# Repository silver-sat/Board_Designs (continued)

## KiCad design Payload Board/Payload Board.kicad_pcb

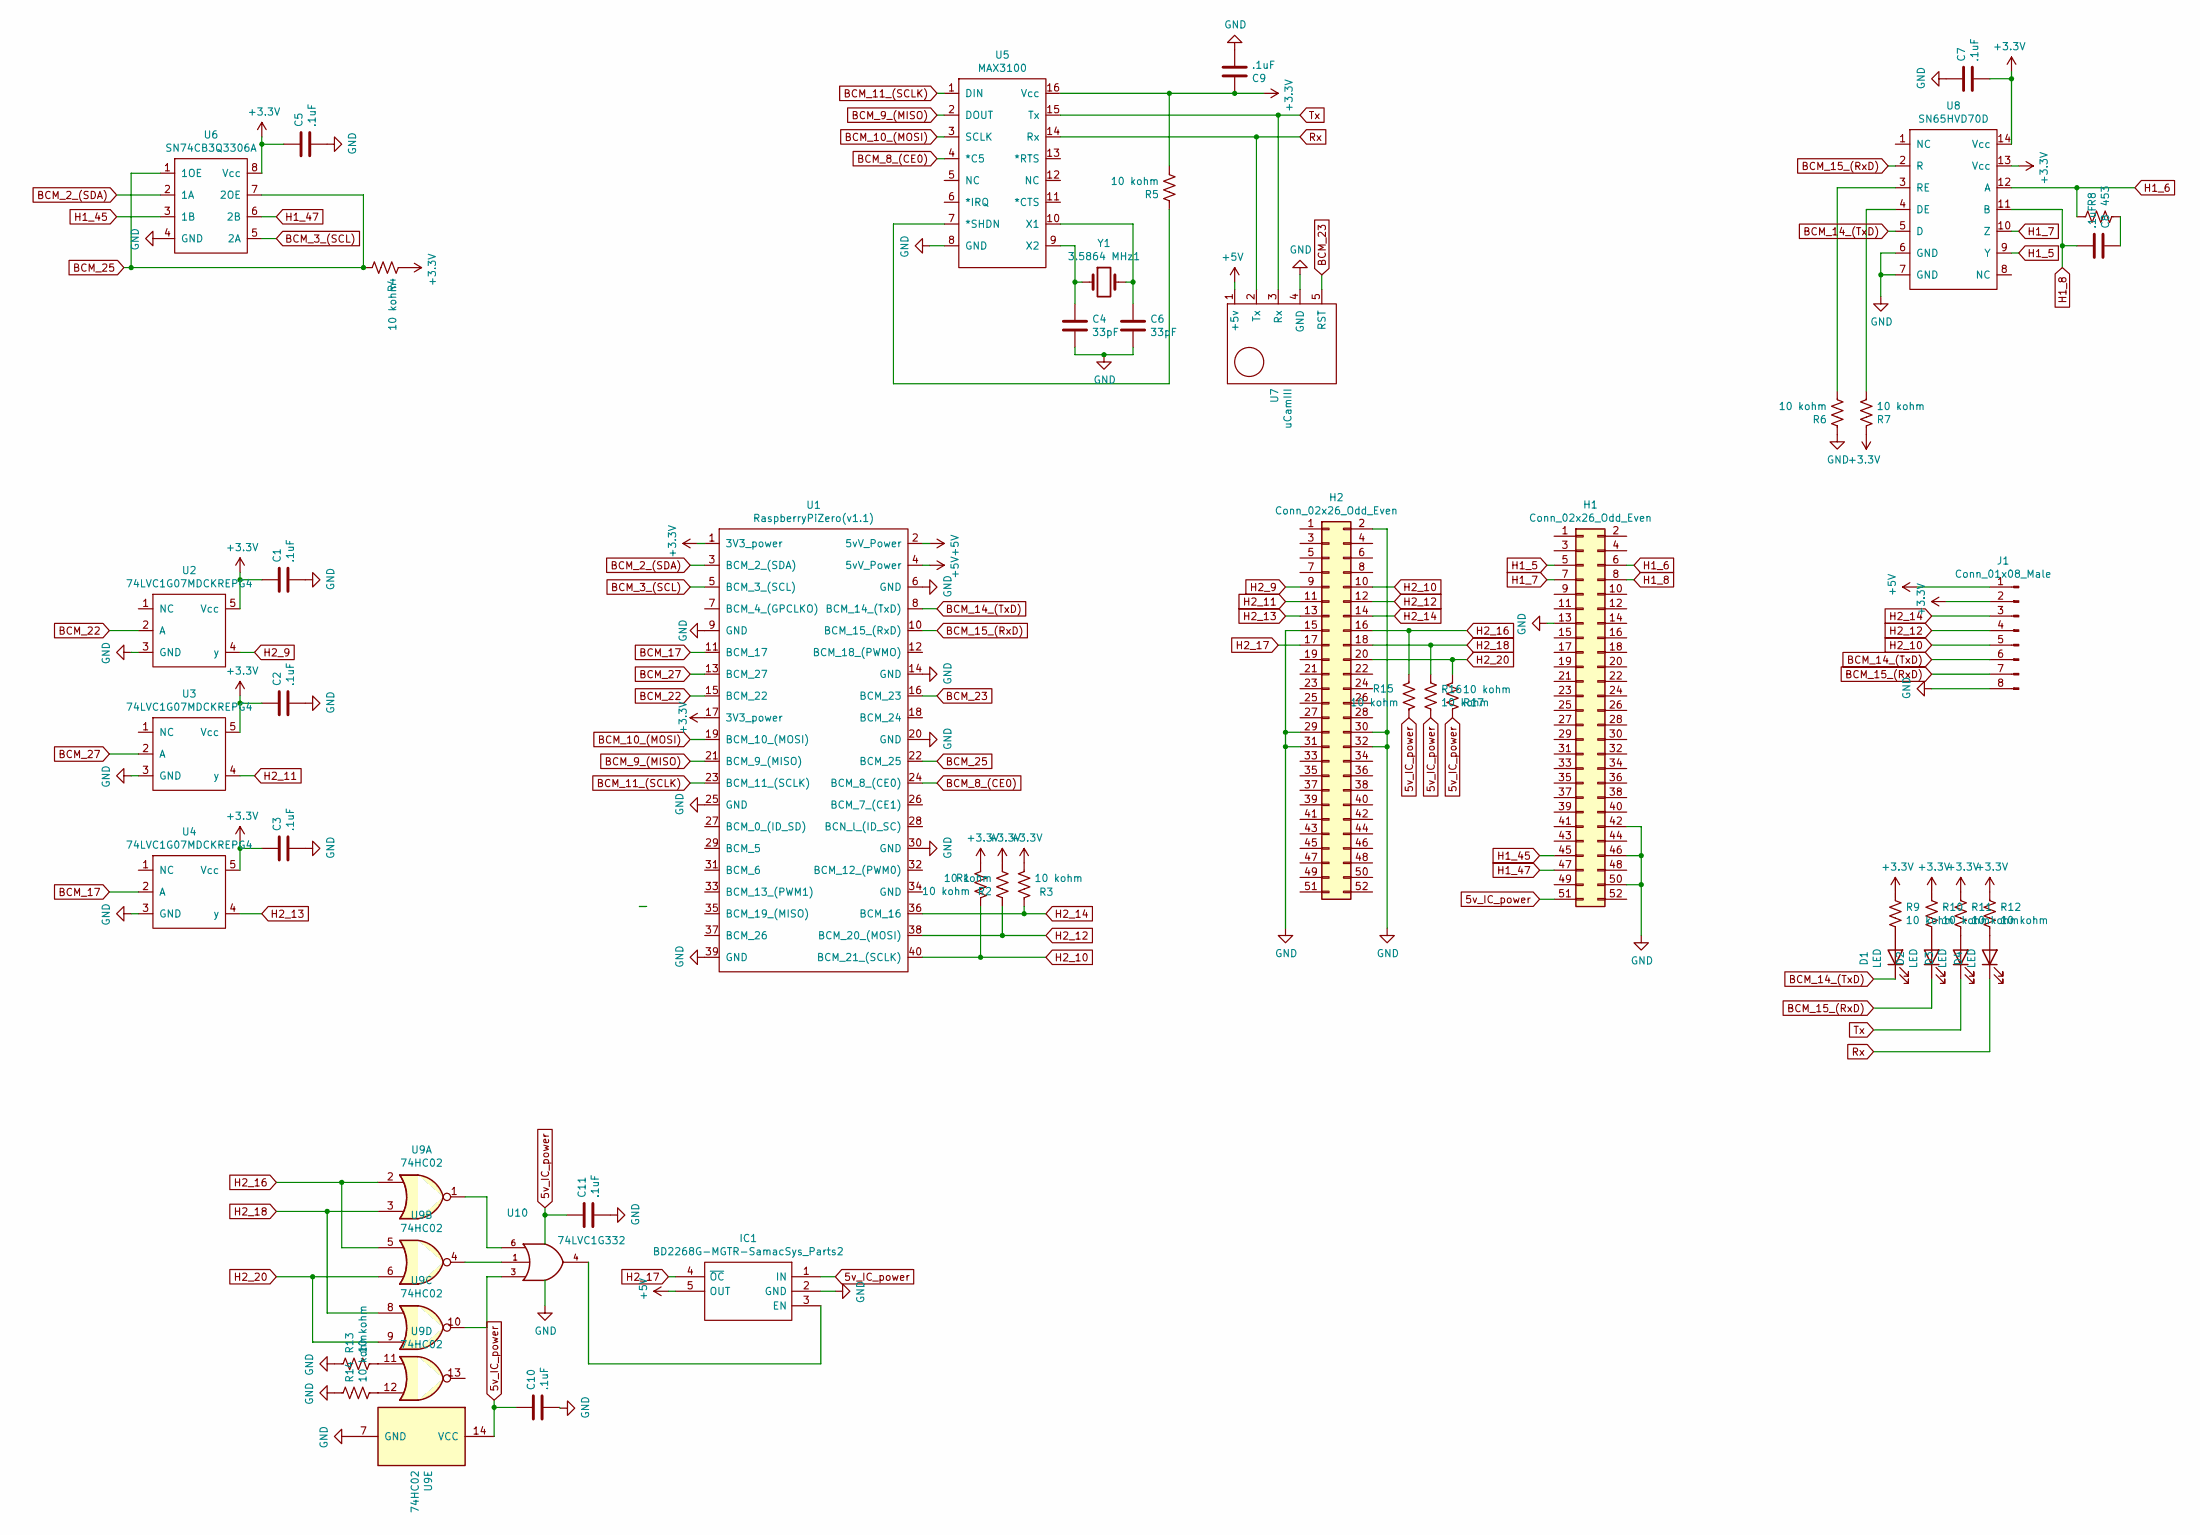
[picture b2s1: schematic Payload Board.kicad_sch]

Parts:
C1, C2, C3, C5, C7, C8, C9, C10, C11: .1uF; C_0603_1608Metric
C4, C6: 33pF; C_0603_1608Metric
D1, D2, D3, D4: LED; LED_D3.0mm
H1, H2: Conn_02x26_Odd_Even; TheBus2x26
IC1: BD2268G-MGTR-SamacSys_Parts2; TSOP-5_1.65x3.05mm_P0.95mm; Manufacturer_Part_Number BD2268G-MGTR; Mouser Part Number 755-BD2268G-MGTR
J1: Conn_01x08_Male; PinHeader_1x08_P2.54mm_Vertical
R1, R2, R3, R4, R5, R6, R7, R9, R10, R11, R12, R13, R14, R15, R16, R17: 10 kohm; R_0603_1608Metric
R8: 453; R_0603_1608Metric
U1: RaspberryPiZero(v1.1); Raspberry_Pi_Zero_Socketed_THT_FaceDown_MountingHoles
U2, U3, U4: 74LVC1G07MDCKREPG4; SOT-353_SC-70-5
U5: MAX3100; QSOP-16_3.9x4.9mm_P0.635mm
U6: SN74CB3Q3306A; TSSOP-8_4.4x3mm_P0.65mm
U7: uCamIII; UCAM-III
U8: SN65HVD70D; SOIC-14_3.9x8.7mm_P1.27mm
U9: 74HC02; SOIC-14_3.9x8.7mm_P1.27mm
U10: 74LVC1G332; SOT-23-6
Y1: 3.5864 MHz1; Crystal_SMD_HC49-SD_HandSoldering

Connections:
5v_IC_power: C10.1, C11.1, H1.51, IC1.1 (IN), R15.2, R16.2, R17.1, U9.14 (VCC), U10.5 (VCC)
+3V3: C1.1, C2.1, C3.1, C5.1, C7.2, C9.1, J1.2, R1.1, R2.2, R3.2, R4.1, R5.2, R7.1, R9.1, R10.1, R11.1, R12.1, U1.1 (3V3_power), U1.17 (3V3_power), U2.5 (Vcc), U3.5 (Vcc), U4.5 (Vcc), U5.16 (Vcc), U6.8 (Vcc), U8.13 (Vcc), U8.14 (Vcc)
+5V: IC1.5 (OUT), J1.1, U1.2 (5vV_Power), U1.4 (5vV_Power), U7.1 (+5v)
BCM_2_(SDA): U1.3 (BCM_2_(SDA)), U6.2 (1A)
BCM_3_(SCL): U1.5 (BCM_3_(SCL)), U6.5 (2A)
BCM_8_(CE0): U1.24 (BCM_8_(CE0)), U5.4 (*C5)
BCM_9_(MISO): U1.21 (BCM_9_(MISO)), U5.2 (DOUT)
BCM_10_(MOSI): U1.19 (BCM_10_(MOSI)), U5.3 (SCLK)
BCM_11_(SCLK): U1.23 (BCM_11_(SCLK)), U5.1 (DIN)
BCM_14_(TxD): D1.1 (K), J1.6, U1.8 (BCM_14_(TxD)), U8.5 (D)
BCM_15_(RxD): D2.1 (K), J1.7, U1.10 (BCM_15_(RxD)), U8.2 (R)
BCM_17: U1.11 (BCM_17), U4.2 (A)
BCM_22: U1.15 (BCM_22), U2.2 (A)
BCM_23: U1.16 (BCM_23), U7.5 (RST)
BCM_25: R4.2, U1.22 (BCM_25), U6.1 (1OE), U6.7 (2OE)
BCM_27: U1.13 (BCM_27), U3.2 (A)
GND: C1.2, C2.2, C3.2, C4.2, C5.2, C6.2, C7.1, C9.2, C10.2, C11.2, H1.13, H1.42, H1.46, H1.50, H2.2, H2.15, H2.29, H2.30, H2.31, H2.32, IC1.2 (GND), J1.8, R6.1, R13.1, R14.1, U1.6 (GND), U1.9 (GND), U1.14 (GND), U1.20 (GND), U1.25 (GND), U1.30 (GND), U1.39 (GND), U2.3 (GND), U3.3 (GND), U4.3 (GND), U5.8 (GND), U6.4 (GND), U7.4 (GND), U8.6 (GND), U8.7 (GND), U9.7 (GND), U10.2 (GND)
H1_5: H1.5, U8.9 (Y)
H1_6: H1.6, R8.1, U8.12 (A)
H1_7: H1.7, U8.10 (Z)
H1_8: C8.2, H1.8, U8.11 (B)
H1_45: H1.45, U6.3 (1B)
H1_47: H1.47, U6.6 (2B)
H2_9: H2.9, U2.4 (y)
H2_10: H2.10, J1.5, R1.2, U1.40 (BCM_21_(SCLK))
H2_11: H2.11, U3.4 (y)
H2_12: H2.12, J1.4, R2.1, U1.38 (BCM_20_(MOSI))
H2_13: H2.13, U4.4 (y)
H2_14: H2.14, J1.3, R3.1, U1.36 (BCM_16)
H2_16: H2.16, R15.1, U9.2, U9.5
H2_17: H2.17, IC1.4 (~OC)
H2_18: H2.18, R16.1, U9.3, U9.8
H2_20: H2.20, R17.2, U9.6, U9.9
unnamed: C4.1, U5.9 (X2), Y1.1
unnamed: C6.1, U5.10 (X1), Y1.2
unnamed: C8.1, R8.2
unnamed: D1.2 (A), R9.2
unnamed: D2.2 (A), R10.2
unnamed: D3.2 (A), R11.2
unnamed: D4.2 (A), R12.2
unnamed: IC1.3 (EN), U10.4
unnamed: R5.1, U5.7 (*SHDN)
unnamed: R6.2, U8.3 (RE)
unnamed: R7.2, U8.4 (DE)
unnamed: R13.2, U9.11
unnamed: R14.2, U9.12
unnamed: U9.4, U10.1
unnamed: U9.10, U10.3
unnamed: U9.1, U10.6
Rx: D4.1 (K), U5.14 (Rx), U7.2 (Tx)
Tx: D3.1 (K), U5.15 (Tx), U7.3 (Rx)

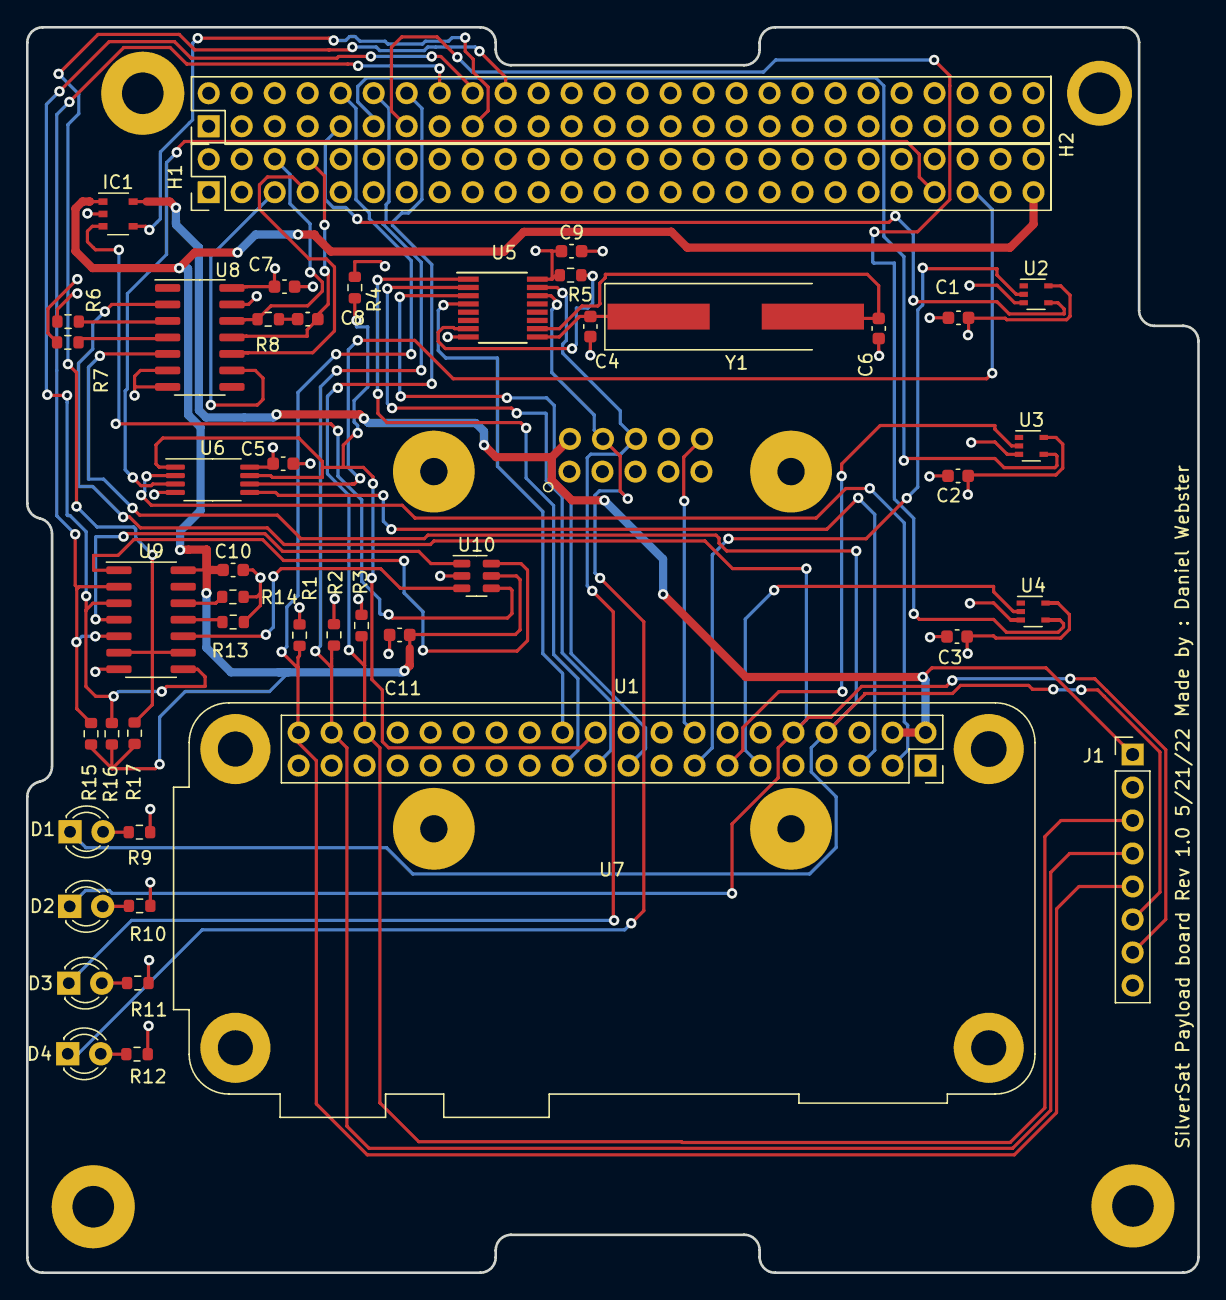
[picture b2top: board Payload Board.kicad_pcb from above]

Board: 4 copper layers, 90.2 x 95.9 mm, 47 parts (0 on the bottom side), 51 nets.

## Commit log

2022-02-24 Initial Commit of the Avionics Board
2022-02-26 Deleting the footprints.pretty directory in this folder
    This directory is a duplicate of the one in kicad_library
2022-03-09 Update Payload board to Board GIT hub
2022-03-09 initial commit of I^2, GPIO, and buffer
2022-03-09 Finished work For Avionics Board(Danny)
2022-03-09 Test
2022-03-15 Update Microcontroller.sch
    Initial commit for the microcontroller sheet
2022-03-15 Create Microcontroller.sch-bak
    Initial commit microcontroller.sch-bak
2022-03-15 Update Avionics_Board-cache.lib
    commiting board cache
2022-03-19 Adding in a Comms Board
    Created and added top hierarchical sheet
2022-03-19 Updated radio chip to AX5043
    I updated the top-level radio schematic so that it uses the AX5043. All of the other files are unchanged.
2022-03-26 Modified directory name
    Modified the directory name to indicate that we should be using the hierarchical schematic, Silversat_Comms, not this one. This directory was added for reference.
2022-03-26 Updated microcontroller design
2022-03-29 Replace Files
2022-04-01 Ported to new Kicad
    Versions that have been imported/opened in Kicad 6
2022-04-02 Converted to KiCAD 6. Added pins to microcontroller sheet
2022-04-04 Added connections to H1/H2, Changed uC SERCOM pins. Added titles
2022-04-05 Shifted AX5043 ever so slightly to the right
2022-04-06 Delete AX5043.pro
    This should not be a separate project file
2022-04-06 Delete AX5043.kicad_pro
    This should not be a separate project, but part of SilverSat_Comms
2022-04-09 Added 3.3V eFuse, part numbers
2022-04-09 Added power switch to 3.3V eFuse for alternate USB power
2022-04-10 Updated RTC parts values, added test LEDS, test points, and header
2022-04-11 Adding logic
2022-04-13 Added mounting holes
2022-04-16 resolving conflicts on Avionics board schematic
2022-04-16 Initial commit of SilverSat_Template
2022-04-16 Attempt to resolve conflicts
2022-04-16 New commits for Avionics_Board and Avionics_Internal I2C
2022-04-18 Added camera clearance hole, included Avionics dxf file
2022-04-19 Added DIP option to RTC. Updated cap values on eFuse.
2022-04-19 Updated Part Numbers, added footprints for SWD and ICSP headers
2022-04-20 Re-uploaded entire schematic
    I have re-uploaded the entire schematic because I do not know what files is the current radio schematic.
2022-04-23 Final? update to 5v switch
2022-04-23 Deleted one line that was excessive.
2022-04-23 Full system hierarchy
    I've added a top level, full system hierarchical schematic.
    To make this work, I added sheet connections to all levels of the hierarchy, but so as not to upset anyone's current work, I saved the affected schematics to the top level (payload and avionics). As 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
    I've also brought in my most recent changes to comms to add the drivers for the serial ports and to reflect the same signal naming convention (pin name_header-headerpin).
2022-04-23 Delete SilverSat_Radio_Module.kicad_pcb
    Removed by tkc to consolidate files
2022-04-23 Delete SilverSat_Radio_Module.kicad_pro
    Removed by tkc to consolidate files
2022-04-23 Delete SilverSat_Radio_Module.kicad_sch
    Removed by tkc to consolidate files
2022-04-23 Delete SilverSat_Radio_Module.pro
    Removed by tkc to consolidate files
2022-04-23 Delete SilverSat_Radio_Module.sch
    Removed by tkc to consolidate files
2022-04-23 Delete SilverSat_Radio_Module.sch.pdf
    Removed by tkc to consolidate files
2022-04-23 Delete SilverSat_Radio_Module.sch-bak
    Removed by tkc to consolidate files
2022-04-23 Delete SilverSat_Radio_Module.kicad_prl
    Removed by tkc to consolidate files
2022-04-23 Delete SilverSat_Radio_Module-cache.lib
    Removed by tkc to consolidate files
2022-04-23 Delete Processor.sch-bak
    Removed by tkc to consolidate files
2022-04-23 Delete Processor.kicad_sch
    Removed by tkc to consolidate files
2022-04-23 Delete Power_Amp.kicad_sch
    Removed by tkc to consolidate files
2022-04-23 Delete Power_Amp.sch
    Removed by tkc to consolidate files
2022-04-23 Delete Power_Amp.sch-bak
    Removed by tkc to consolidate files
2022-04-23 Delete Processor.sch
    Removed by tkc to consolidate files
2022-04-23 Delete Radio.kicad_sch
    Removed by tkc to consolidate files
2022-04-23 Delete Radio.sch
    Removed by tkc to consolidate files
2022-04-23 Delete Radio.sch-bak
    Removed by tkc to consolidate files
2022-04-23 net names
    Added some net names
2022-04-23 import of samd21 from avionics
    Imported the avionics version of the samd21 schematic.
2022-04-24 Imported DXF of board shape
2022-04-27 A bunch of Changes, mostly annotation and footprint assignment
2022-04-29 efuse import
    imported the efuse schematics from the power directory (no changes made other than to put the signals close to where they should go).
    Some parts may be removed.
2022-04-30 I fixed some of the errors and warnings in the DRC function.
2022-04-30 Dev board copy in progress
    Copying schematic from AX5043 433 MHz dev board datasheet (https://www.onsemi.com/pub/collateral/add5043-433-2-gevk%20schematic.pdf)
2022-04-30 LED Fix
2022-05-04 clean up
    I removed all references to a separate AX5043 project. All changes should be through the hierarchical schematic. The schematic is still there, but KiCad hides the subsheet schematics in a hierarchica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
    I also turned off the local project libraries altogether, so hopefully that error (on load) will go away.
2022-05-04 Update SilverSat_Comms.kicad_pcb
    I forgot to move the board with the imported dxf layer into the pcb project file.
2022-05-04 design rules added
    I added design rules consistent with OSHPARK's recommendations, except that I modified the annular ring rule up slightly to 0.005 vs 0.004
2022-05-04 Update SilverSat_Comms.kicad_pro
    Adjusted default net class rule so that the right linewidth and via are chosen
2022-05-07 Updated in-progress AX5043 dev board copy
2022-05-07 Added zip files to .gitignore
2022-05-07 Pcb Population
    working on the pcb
2022-05-07 Merging old files from dev into main
    The merges all the old working files from dev into main. I also deleted any remaining legacy .pro files and the AX5043.pro file as well. All work should be started from the Silversat_Comms.pro file.
2022-05-08 MOAR PCB Population
    Added more parts onto the board.(also purple...)
2022-05-11 Adjusted design rules
    Somehow the dielectric color got switched. Looking at the text file it also looks like some board parameters are being changed, but I didn't change them, which is odd
2022-05-14 Boarder restrictions
2022-05-14 Finishing Board Population
2022-05-14 Quick Fix
    part of previous change
2022-05-18 Fuse revision
    Made revisions to the 3V3 and 5V eFuse designs
    Added H1 and H2 headers to main page
2022-05-19 added temp sensor
    picked out a temp sensor that was available (TMP100)
    not much to choose from in an easy to solder package.
2022-05-19 First draft of AX5043 schematic
2022-05-20 TCXO change
2022-05-20 added autosave files to .gitignore
    added autosave files to .gitignore
2022-05-20 Uploaded 2022-05-20 file to main
2022-05-20 copied in latest ax5043 changes
    Copied from schematic in dev branch
2022-05-20 Added extra board pins per datasheet
2022-05-21 samd21 changes
    Modified hierarchical connections on SAMD21 to bring out GPIO to top level and then make connections to other nets on that block. This is an attempt to keep the SAMD21 page clean. Pulled up USB conne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
    Removed global net connector on AX5043 page and connected net to hierarchical rx pin. Added connector (reminder really) on the root page.
    Removed all global power labels (other than grounds) on the SAMD21 page. There should be no global power nets except on the root page.
2022-05-21 Final Changes?
2022-05-21 And So It Begins(Routing)
    Routing begins, and the power, led and usb infrastructure has been finished
2022-05-22 More Routing has been completed
2022-05-23 Updated pours. Generated Gerbers
2022-05-28 More Routing Completed.
2022-05-28 Fixing bad placement and updating MPU footprint
2022-06-03 Changing layout and upgrading to 10 mils
2022-06-04 Changing C10 and more routing
2022-06-08 Even More Routing
2022-06-10 Add public repo. change note
2022-06-15 Attempting to finish right side of SamD and fixing Red/Blue Location
2022-06-15 Fixing Bus Layer Location
2022-06-18 Avionics Board V0.8
    Changes:
    1. Now adding version numbers to Board
    2. CHONK 5V line on 3V3 layer of board to J4 header
    3. Nearly done routing SamD21
    4. Need to complete routing of H1&H2
2022-06-20 Avionics Board V0.85
    Changes:
    1. Changed up/using 3v3 layer for routing
    2. Everything is connected except for USB which should be connected soon!
    3. All errors are fixed EXCEPT FOR: H1&H2 courtyard intersecting(doesn't matter), USB data not connected and one mounting hole pad is too large and escaping the board( and someone was supposed to fix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
    Close to 0.9 which means it will be given to Dave for evaluation.
2022-06-20 Avionics Board 0.9 Released!
    Changes:
    1. If the board is okayed by Dave, the board will be updated to 1.0 and ordered!
    2. USB Data Diff lines have been routed, woooo, and the length is within the 3.81mm length mismatch(2.9926mm, and the differential skew would not open cause its ok I guess)
    3. All warnings and errors(other than relating to H1&H2 and that mounting hole)!
2022-06-22 Avionics Board 0.95 Release!
    Small Description:
    90% 3V3 Rerouting
    10% Moving 3V3 Power Regulators
    So close to being done!
2022-07-06 Avionics Board V0.98
    Wow... we are almost there!
    Patch Notes:
    1.Design nitpicking
    2.Fixing some via placement
    3.Moving Radio_SDA and Radio_SCLK
    4.Moving Bypass Cap C1 to U1(FRAM)
2022-07-06 Avionics Board 0.985
    Sorry for adding another decimal place, but some other design nitpicks came up
    Patch Notes:
    1. Fixing some design nitpicks
    (and nothing else...)
2022-07-09 Avionics Board V1.0 Released!
    Woooo!
    V1.0 has been released along with gerbers for the board!
    Patch Notes:
    1. Moved some lines to prevent coupling to USB Lines
    2. Made Gerbers and DRLs for the V1.0 Avionics Board
2022-07-13 BTS Update 1
    A Behind-The-Scenes Update, not much really...
    Patch Notes:
    1. Updated part numbers for *most* parts
    Thats it!
    Not much going on, just making finding parts easier.
2022-07-16 BTS Update 1.5 Released!
    Eeeh... this isn't number 2 simply because its an extension of the first one.
    Patch Notes:
    1. Added more part numbers to the part list
    2. Changed "Part Number" field to "MPN" field
2023-02-23 File Management
    I did some file management to make it easier to understand.
